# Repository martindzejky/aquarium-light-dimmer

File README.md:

# aquarium-light-dimmer
Simple clock-driven LED dimmer circuit for aquarium lights.

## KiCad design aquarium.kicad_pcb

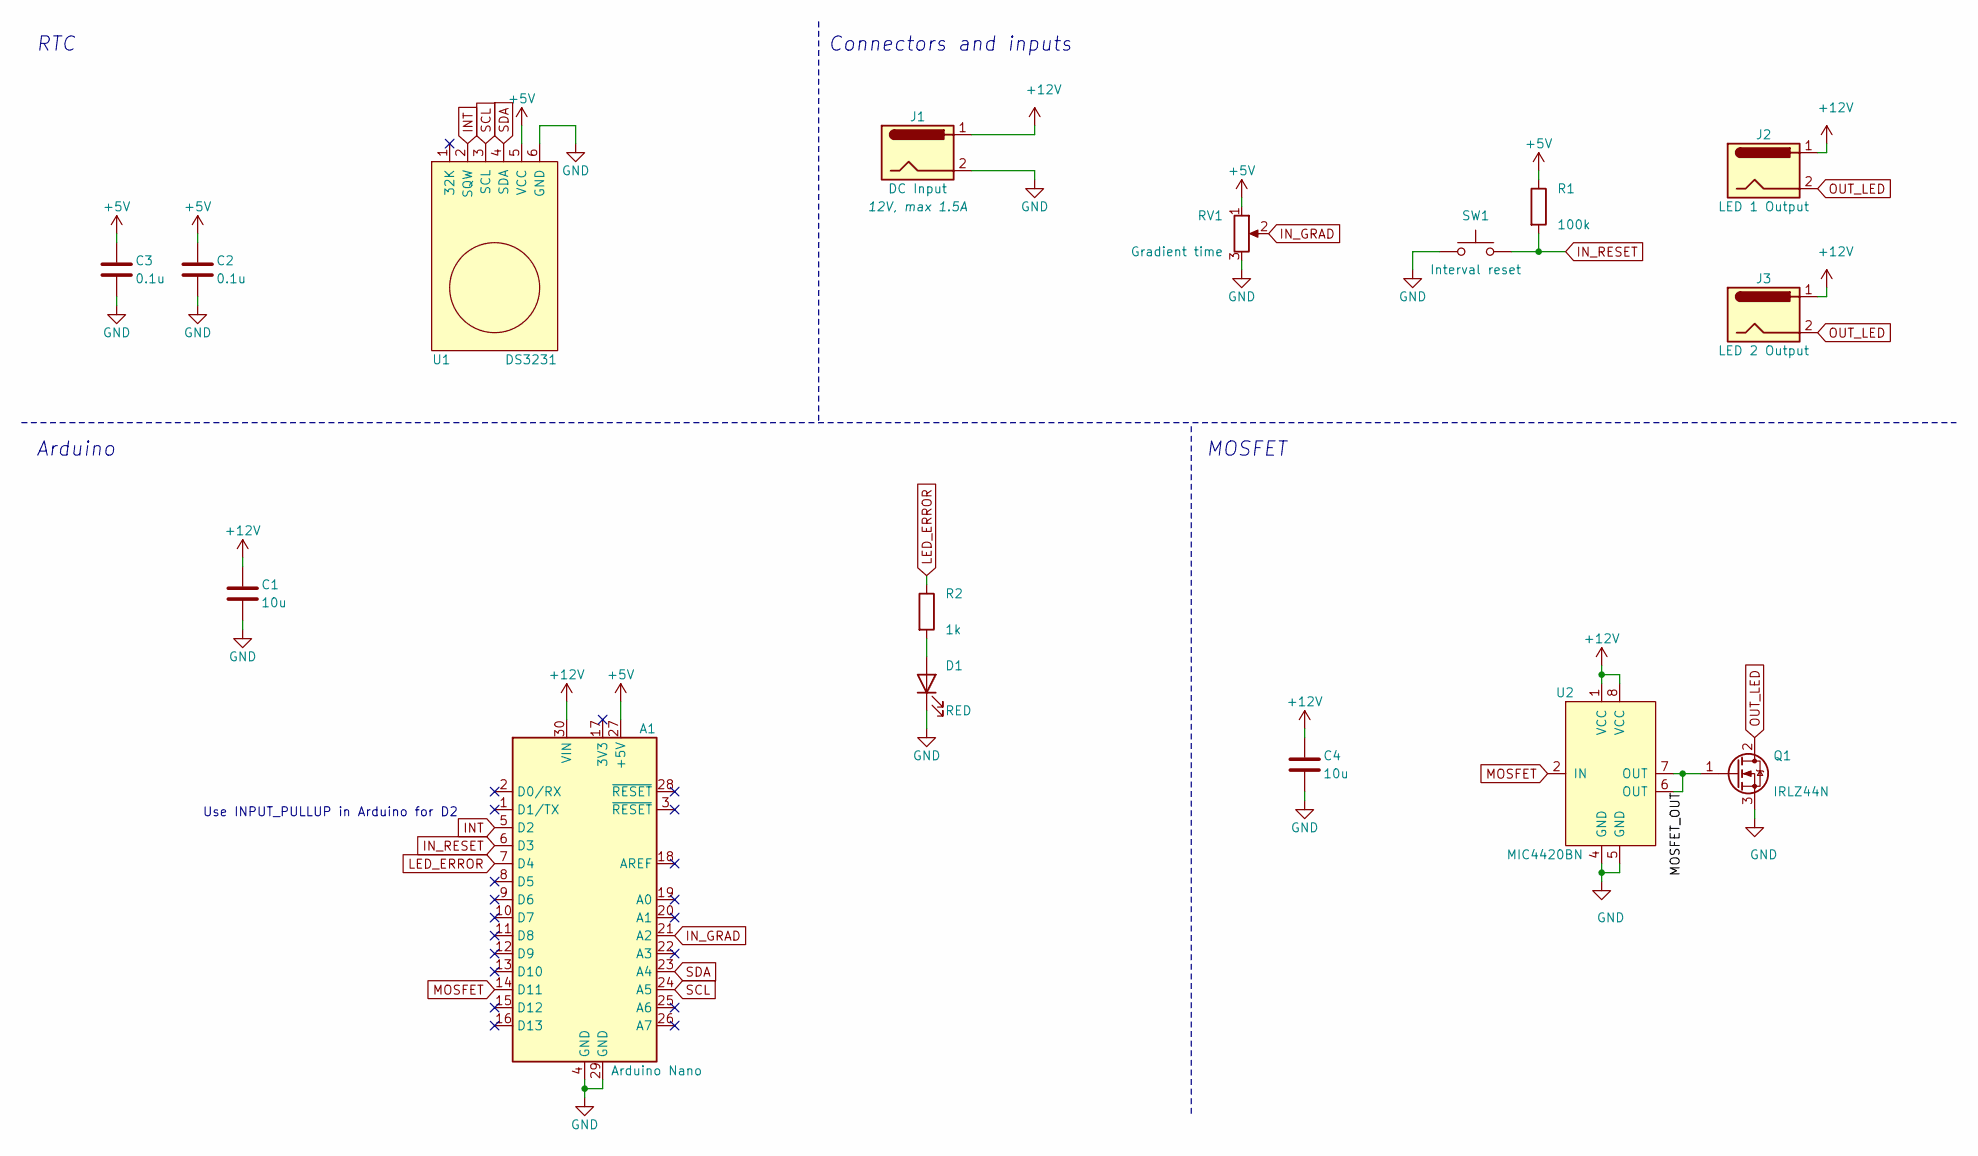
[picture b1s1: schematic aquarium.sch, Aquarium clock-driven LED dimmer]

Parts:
A1: Arduino Nano; Arduino_Nano
C1, C4: 10u; C_Disc_D5.0mm_W2.5mm_P2.50mm
C2, C3: 0.1u; C_Disc_D5.0mm_W2.5mm_P2.50mm
D1: RED; LED_D5.0mm
J1: DC Input; BarrelJack_Horizontal
J2: LED 1 Output; BarrelJack_Horizontal
J3: LED 2 Output; BarrelJack_Horizontal
Q1: IRLZ44N; TO-220-3_Vertical
R1: 100k; R_Axial_DIN0207_L6.3mm_D2.5mm_P10.16mm_Horizontal
R2: 1k; R_Axial_DIN0207_L6.3mm_D2.5mm_P10.16mm_Horizontal
RV1: Gradient time; JST_XH_B3B-XH-A_1x03_P2.50mm_Vertical
SW1: Interval reset; JST_XH_B2B-XH-A_1x02_P2.50mm_Vertical
U1: DS3231; PinHeader_1x06_P2.54mm_Vertical
U2: MIC4420BN; DIP-8_W7.62mm_Socket

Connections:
+5V: A1.27 (+5V), C2.1, C3.1, R1.1, RV1.1, U1.5 (VCC)
+12V: A1.30 (VIN), C1.1, C4.1, J1.1, J2.1, J3.1, U2.1 (VCC), U2.8 (VCC)
/MOSFET_OUT: Q1.1 (G), U2.6 (OUT), U2.7 (OUT)
GND: A1.4 (GND), A1.29 (GND), C1.2, C2.2, C3.2, C4.2, D1.1 (K), J1.2, Q1.3 (S), RV1.3, SW1.1, U1.6 (GND), U2.4 (GND), U2.5 (GND)
INT: A1.5 (D2), U1.2 (SQW)
IN_GRAD: A1.21 (A2), RV1.2
IN_RESET: A1.6 (D3), R1.2, SW1.2
LED_ERROR: A1.7 (D4), R2.1
MOSFET: A1.14 (D11), U2.2 (IN)
unnamed: D1.2 (A), R2.2
OUT_LED: J2.2, J3.2, Q1.2 (D)
SCL: A1.24 (A5), U1.3 (SCL)
SDA: A1.23 (A4), U1.4 (SDA)

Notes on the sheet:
Connectors and inputs
MOSFET
RTC
Arduino
Use INPUT_PULLUP in Arduino for D2

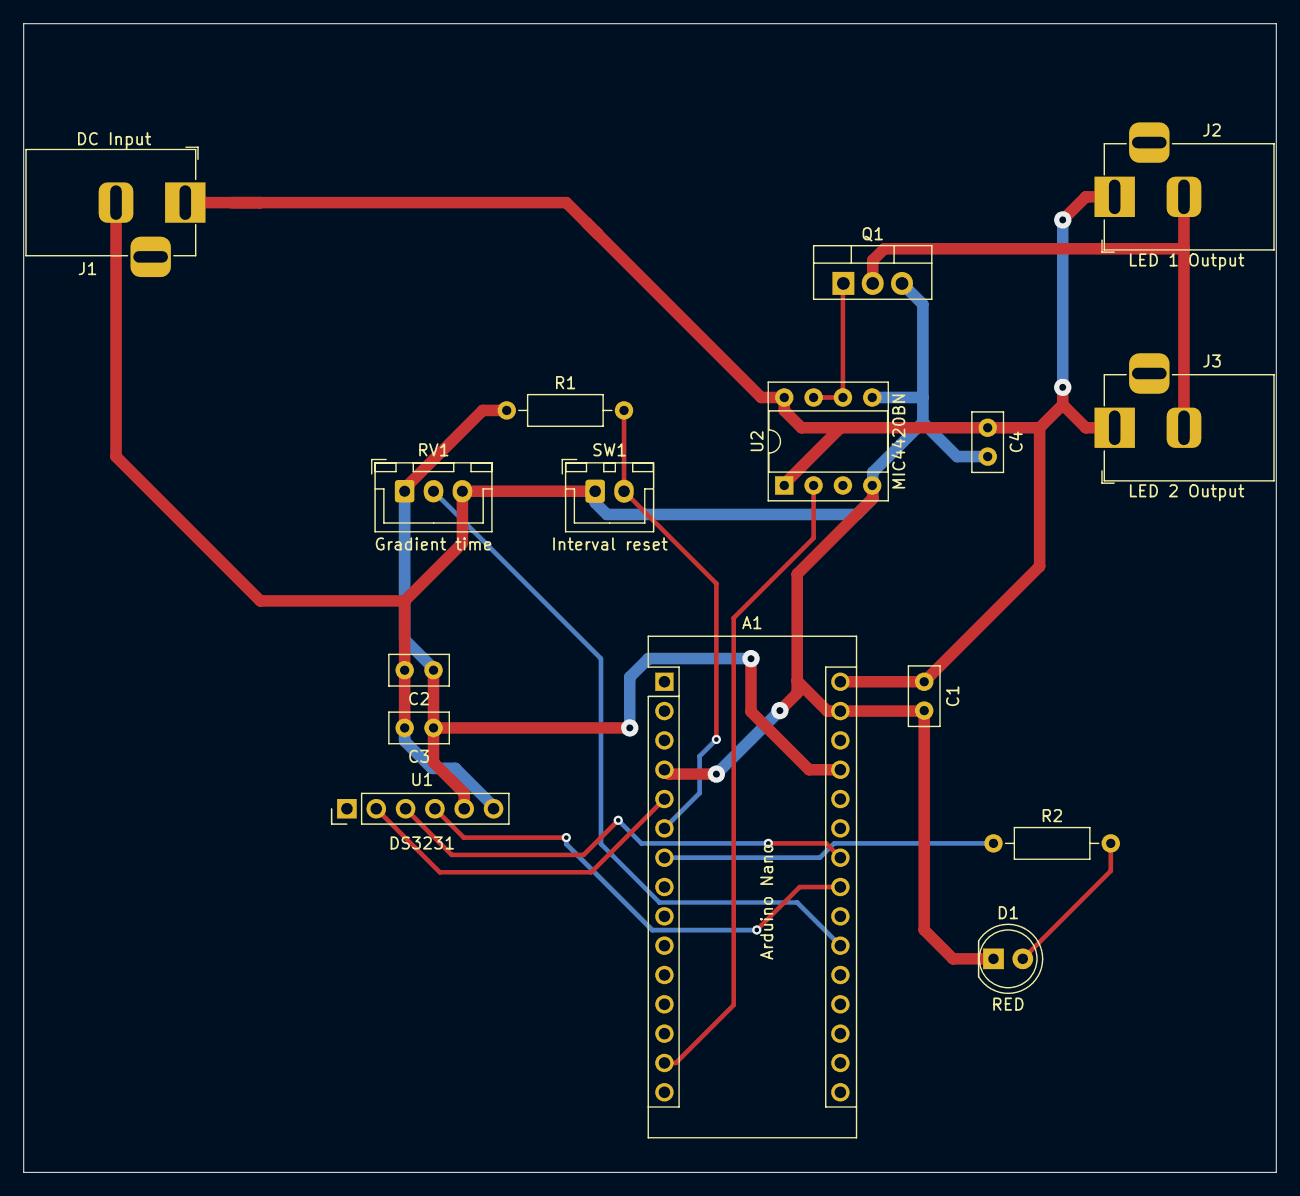
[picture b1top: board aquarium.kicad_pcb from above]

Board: 2 copper layers, 108.5 x 99.5 mm, 16 parts (0 on the bottom side), 13 nets.

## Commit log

2020-10-07 initialize kicad project
2020-10-09 create the electronics schema
2020-10-19 add an error led
2020-10-21 remove the external pullup resistor for the interrupt pin
2020-10-21 assign footprints
2020-10-21 create a simple pcb design
    This is an inspiration for the proofboard
    design I'm going to solder.
2020-10-26 update the schematic to the actual parts used for soldering
2020-10-26 update the pcb design with the new footprints
2020-10-30 add a makefile
2020-10-30 add helper functions
2020-10-30 write ds3231 setup code
2020-10-30 implement the scheduling
2020-10-31 always adjust the time when restarting
2020-10-31 fix analogWrite maximum
    The maximum value for analogWrite is 256.
2020-10-31 tweak the numbers and the formulas
2020-11-21 fix upper bounds of analog write value
